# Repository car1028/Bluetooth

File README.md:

Bluetooth
=========

Bluetooth with AtMega

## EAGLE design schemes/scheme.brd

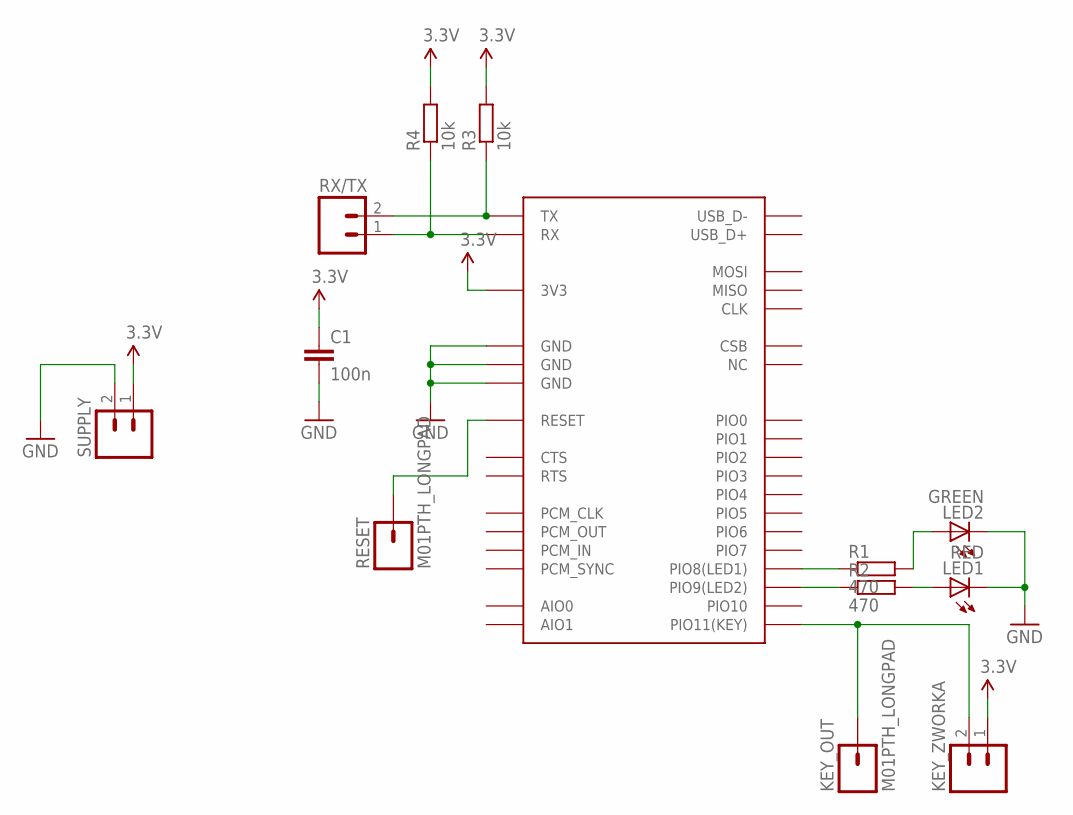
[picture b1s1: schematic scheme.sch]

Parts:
C1: 100n; C0805
IC1: HC-05
KEY_OUT: M01PTH_LONGPAD; 1X01_LONGPAD
KEY_ZWORKA: M02; 1X02_LONGPADS
LED1: RED; CHIPLED_0805
LED2: GREEN; CHIPLED_0805
R1, R2: 470; R0805
R3, R4: 10k; R0805
RESET: M01PTH_LONGPAD; 1X01_LONGPAD
RX/TX: M02; 1X02_LONGPADS
SUPPLY: M02; 1X02_LONGPADS

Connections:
3.3V: C1.1, IC1.3V3, KEY_ZWORKA.1, R3.2, R4.2, SUPPLY.1
GND: C1.2, IC1.GND@1 (GND), IC1.GND@2 (GND), IC1.GND@3 (GND), LED1.C, LED2.C, SUPPLY.2
unnamed: IC1.PIO11(KEY), KEY_OUT.1, KEY_ZWORKA.2
unnamed: IC1.PIO8(LED1), R1.1
unnamed: IC1.PIO9(LED2), R2.1
unnamed: LED2.A, R1.2
unnamed: LED1.A, R2.2
unnamed: IC1.RESET, RESET.1
unnamed: IC1.TX, R3.1, RX/TX.2
unnamed: IC1.RX, R4.1, RX/TX.1

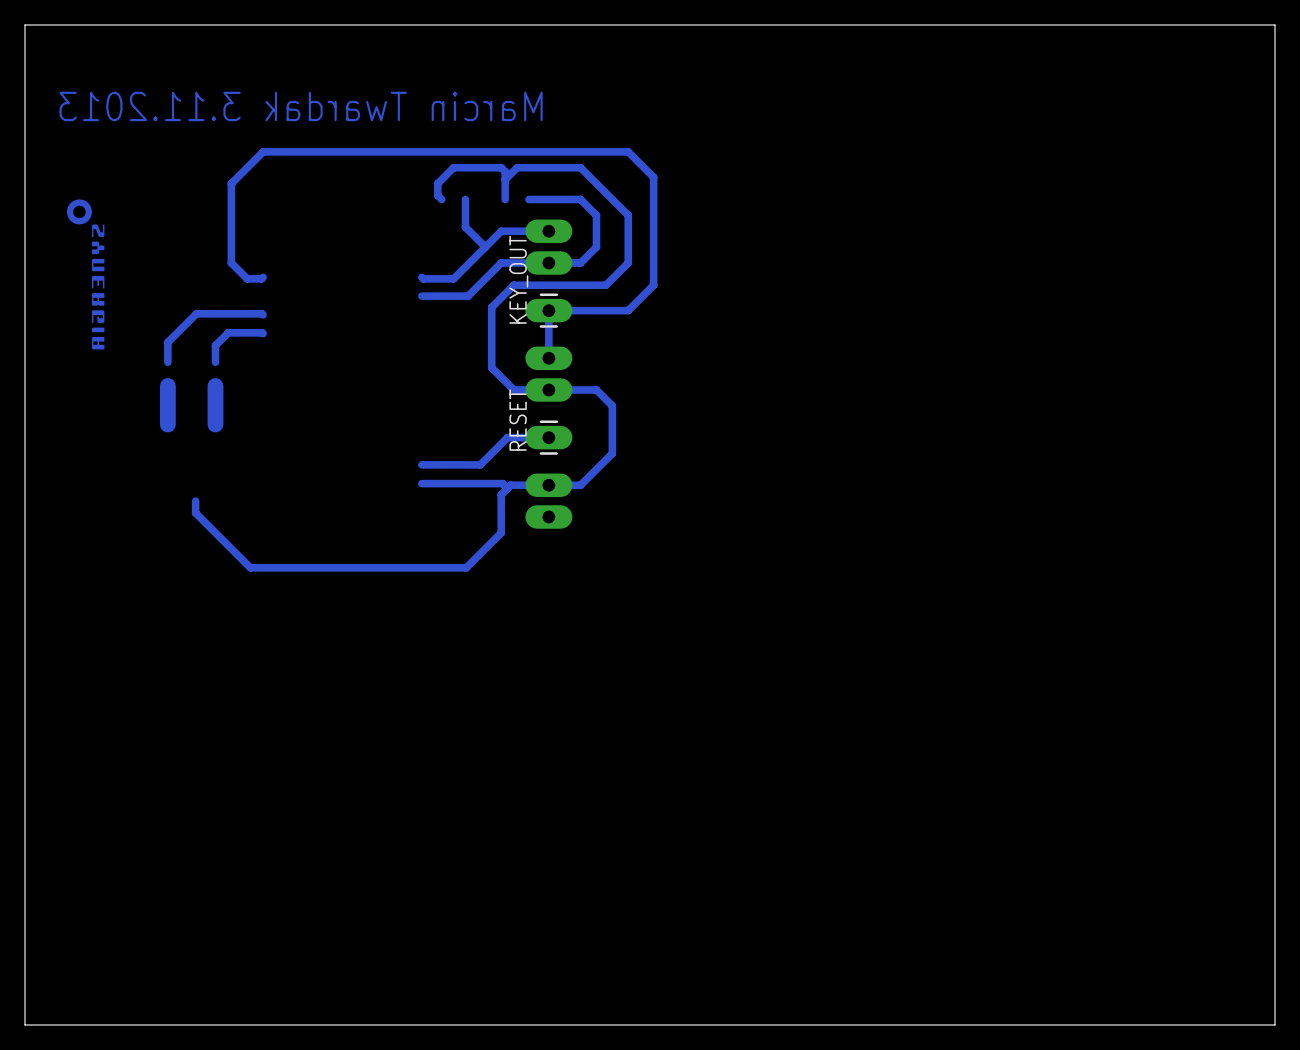
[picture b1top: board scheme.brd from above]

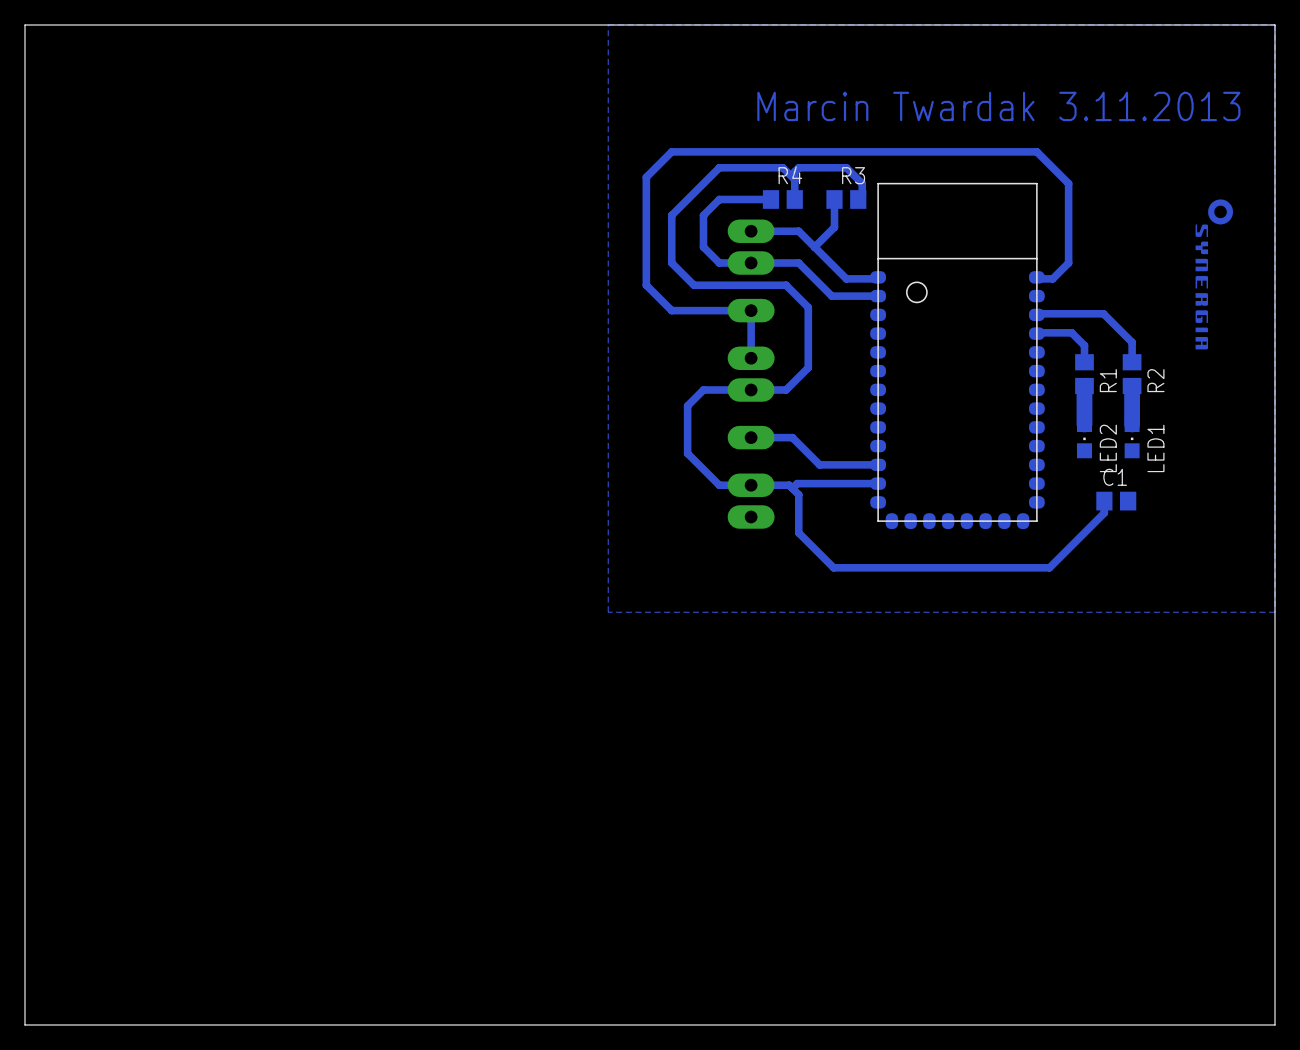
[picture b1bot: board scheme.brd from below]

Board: 2 copper layers, 100.0 x 80.0 mm, 14 parts (9 on the bottom side), 10 nets.

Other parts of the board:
U$1: SYNERGIA_12MM

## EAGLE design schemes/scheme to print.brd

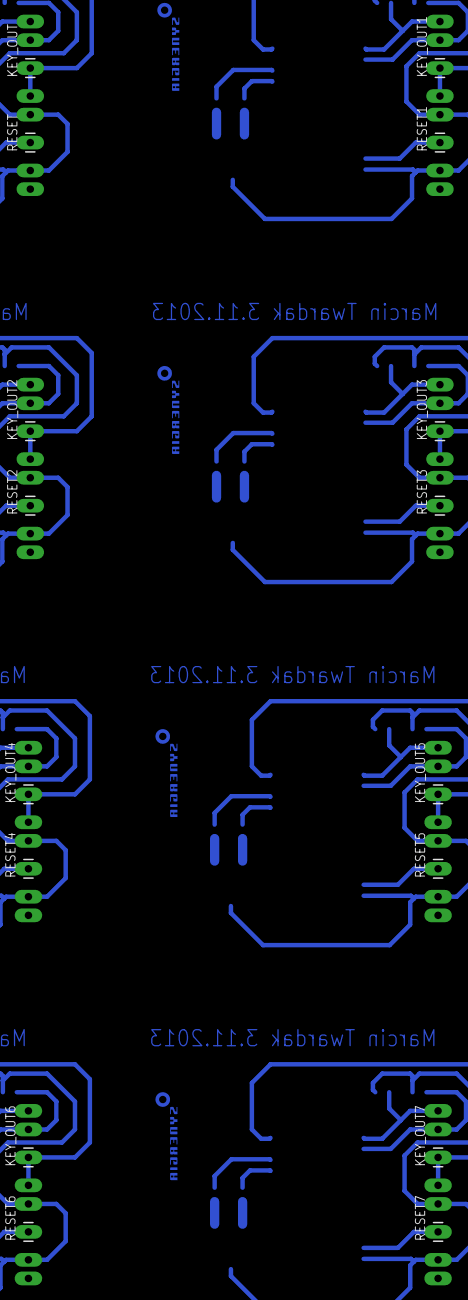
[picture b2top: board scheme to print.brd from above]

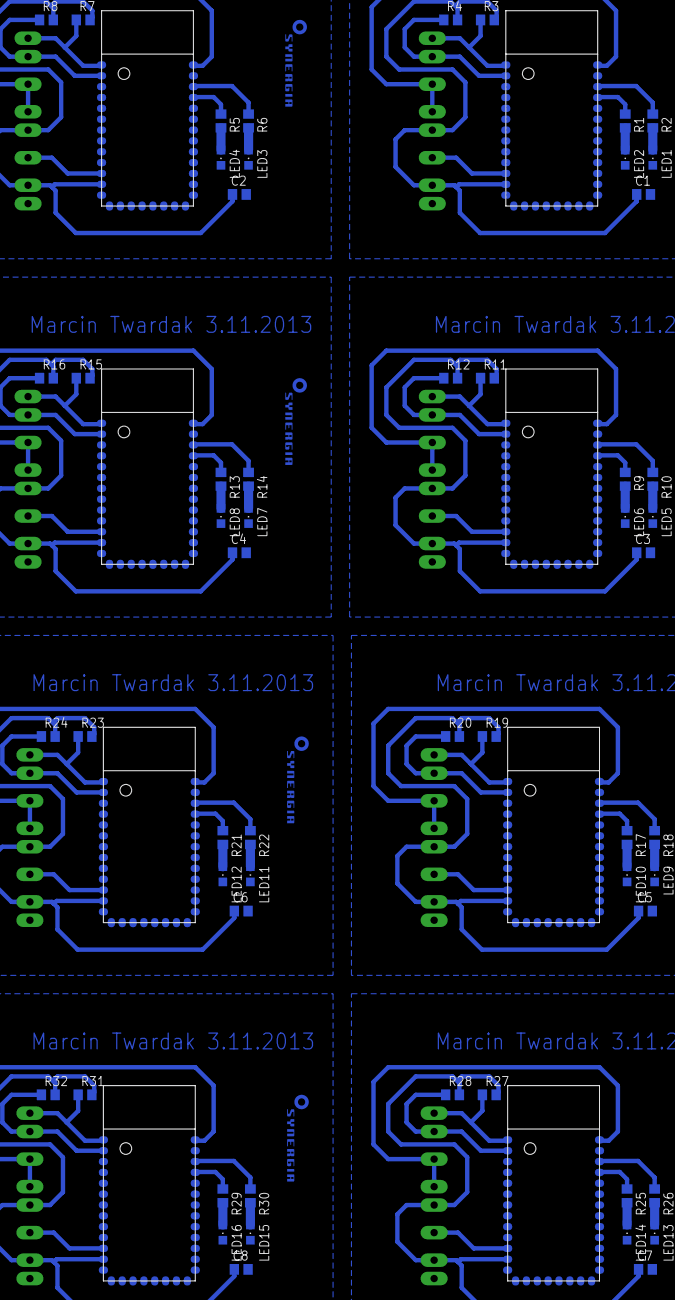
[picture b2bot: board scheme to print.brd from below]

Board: 2 copper layers, 112 parts (72 on the bottom side), 80 nets.

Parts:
C1, C2, C3, C4, C5, C6, C7, C8: 100n; C0805
IC1, IC2, IC3, IC4, IC5, IC6, IC7, IC8: HC-05
KEY_OUT, KEY_OUT1, KEY_OUT2, KEY_OUT3, KEY_OUT4, KEY_OUT5, KEY_OUT6, KEY_OUT7: M01PTH_LONGPAD; 1X01_LONGPAD
KEY_ZWORKA, KEY_ZWORKA1, KEY_ZWORKA2, KEY_ZWORKA3, KEY_ZWORKA4, KEY_ZWORKA5, KEY_ZWORKA6, KEY_ZWORKA7: 1X02_LONGPADS
LED1, LED3, LED5, LED7, LED9, LED11, LED13, LED15: RED; CHIPLED_0805
LED2, LED4, LED6, LED8, LED10, LED12, LED14, LED16: GREEN; CHIPLED_0805
R1, R2, R5, R6, R9, R10, R13, R14, R17, R18, R21, R22, R25, R26, R29, R30: 470; R0805
R3, R4, R7, R8, R11, R12, R15, R16, R19, R20, R23, R24, R27, R28, R31, R32: 10k; R0805
RESET, RESET1, RESET2, RESET3, RESET4, RESET5, RESET6, RESET7: M01PTH_LONGPAD; 1X01_LONGPAD
RX/TX, RX/TX1, RX/TX2, RX/TX3, RX/TX4, RX/TX5, RX/TX6, RX/TX7: 1X02_LONGPADS
SUPPLY, SUPPLY1, SUPPLY2, SUPPLY3, SUPPLY4, SUPPLY5, SUPPLY6, SUPPLY7: 1X02_LONGPADS
U$1, U$2, U$3, U$4, U$5, U$6, U$7, U$8: SYNERGIA_12MM

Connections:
3.3V: C1.1, IC1.3V3, KEY_ZWORKA.1, R3.2, R4.2, SUPPLY.1
3.3V1: C2.1, IC2.3V3, KEY_ZWORKA1.1, R7.2, R8.2, SUPPLY1.1
3.3V2: C3.1, IC3.3V3, KEY_ZWORKA2.1, R11.2, R12.2, SUPPLY2.1
3.3V3: C4.1, IC4.3V3, KEY_ZWORKA3.1, R15.2, R16.2, SUPPLY3.1
3.3V4: C5.1, IC5.3V3, KEY_ZWORKA4.1, R19.2, R20.2, SUPPLY4.1
3.3V5: C6.1, IC6.3V3, KEY_ZWORKA5.1, R23.2, R24.2, SUPPLY5.1
3.3V6: C7.1, IC7.3V3, KEY_ZWORKA6.1, R27.2, R28.2, SUPPLY6.1
3.3V7: C8.1, IC8.3V3, KEY_ZWORKA7.1, R31.2, R32.2, SUPPLY7.1
GND: C1.2, IC1.GND@1, IC1.GND@2, IC1.GND@3, LED1.C, LED2.C, SUPPLY.2
GND1: C2.2, IC2.GND@1, IC2.GND@2, IC2.GND@3, LED3.C, LED4.C, SUPPLY1.2
GND2: C3.2, IC3.GND@1, IC3.GND@2, IC3.GND@3, LED5.C, LED6.C, SUPPLY2.2
GND3: C4.2, IC4.GND@1, IC4.GND@2, IC4.GND@3, LED7.C, LED8.C, SUPPLY3.2
GND4: C5.2, IC5.GND@1, IC5.GND@2, IC5.GND@3, LED9.C, LED10.C, SUPPLY4.2
GND5: C6.2, IC6.GND@1, IC6.GND@2, IC6.GND@3, LED11.C, LED12.C, SUPPLY5.2
GND6: C7.2, IC7.GND@1, IC7.GND@2, IC7.GND@3, LED13.C, LED14.C, SUPPLY6.2
GND7: C8.2, IC8.GND@1, IC8.GND@2, IC8.GND@3, LED15.C, LED16.C, SUPPLY7.2
unnamed: IC1.PIO11(KEY), KEY_OUT.1, KEY_ZWORKA.2
unnamed: IC1.PIO8(LED1), R1.1
unnamed: IC1.PIO9(LED2), R2.1
unnamed: LED2.A, R1.2
unnamed: LED1.A, R2.2
unnamed: IC1.RESET, RESET.1
unnamed: IC1.TX, R3.1, RX/TX.2
unnamed: IC1.RX, R4.1, RX/TX.1
unnamed: IC2.PIO11(KEY), KEY_OUT1.1, KEY_ZWORKA1.2
unnamed: IC2.PIO8(LED1), R5.1
unnamed: IC2.PIO9(LED2), R6.1
unnamed: LED3.A, R6.2
unnamed: LED4.A, R5.2
unnamed: IC2.TX, R7.1, RX/TX1.2
unnamed: IC2.RX, R8.1, RX/TX1.1
unnamed: IC2.RESET, RESET1.1
unnamed: IC3.PIO11(KEY), KEY_OUT2.1, KEY_ZWORKA2.2
unnamed: IC3.PIO8(LED1), R9.1
unnamed: IC3.PIO9(LED2), R10.1
unnamed: LED5.A, R10.2
unnamed: LED6.A, R9.2
unnamed: IC3.TX, R11.1, RX/TX2.2
unnamed: IC3.RX, R12.1, RX/TX2.1
unnamed: IC3.RESET, RESET2.1
unnamed: IC4.PIO11(KEY), KEY_OUT3.1, KEY_ZWORKA3.2
unnamed: IC4.PIO8(LED1), R13.1
unnamed: IC4.PIO9(LED2), R14.1
unnamed: LED7.A, R14.2
unnamed: LED8.A, R13.2
unnamed: IC4.TX, R15.1, RX/TX3.2
unnamed: IC4.RX, R16.1, RX/TX3.1
unnamed: IC4.RESET, RESET3.1
unnamed: IC5.PIO11(KEY), KEY_OUT4.1, KEY_ZWORKA4.2
unnamed: IC5.PIO8(LED1), R17.1
unnamed: IC5.PIO9(LED2), R18.1
unnamed: LED9.A, R18.2
unnamed: LED10.A, R17.2
unnamed: IC5.TX, R19.1, RX/TX4.2
unnamed: IC5.RX, R20.1, RX/TX4.1
unnamed: IC5.RESET, RESET4.1
unnamed: IC6.PIO11(KEY), KEY_OUT5.1, KEY_ZWORKA5.2
unnamed: IC6.PIO8(LED1), R21.1
unnamed: IC6.PIO9(LED2), R22.1
unnamed: LED11.A, R22.2
unnamed: LED12.A, R21.2
unnamed: IC6.TX, R23.1, RX/TX5.2
unnamed: IC6.RX, R24.1, RX/TX5.1
unnamed: IC6.RESET, RESET5.1
unnamed: IC7.PIO11(KEY), KEY_OUT6.1, KEY_ZWORKA6.2
unnamed: IC7.PIO8(LED1), R25.1
unnamed: IC7.PIO9(LED2), R26.1
unnamed: LED13.A, R26.2
unnamed: LED14.A, R25.2
unnamed: IC7.TX, R27.1, RX/TX6.2
unnamed: IC7.RX, R28.1, RX/TX6.1
unnamed: IC7.RESET, RESET6.1
unnamed: IC8.PIO11(KEY), KEY_OUT7.1, KEY_ZWORKA7.2
unnamed: IC8.PIO8(LED1), R29.1
unnamed: IC8.PIO9(LED2), R30.1
unnamed: LED15.A, R30.2
unnamed: LED16.A, R29.2
unnamed: IC8.TX, R31.1, RX/TX7.2
unnamed: IC8.RX, R32.1, RX/TX7.1
unnamed: IC8.RESET, RESET7.1

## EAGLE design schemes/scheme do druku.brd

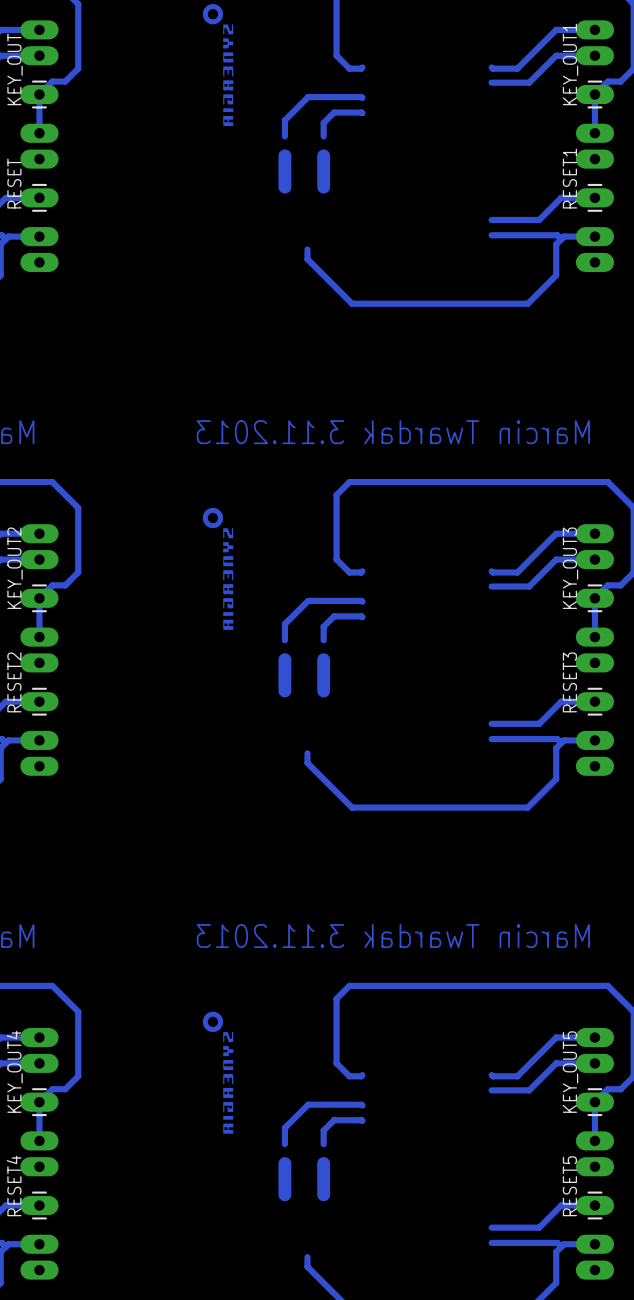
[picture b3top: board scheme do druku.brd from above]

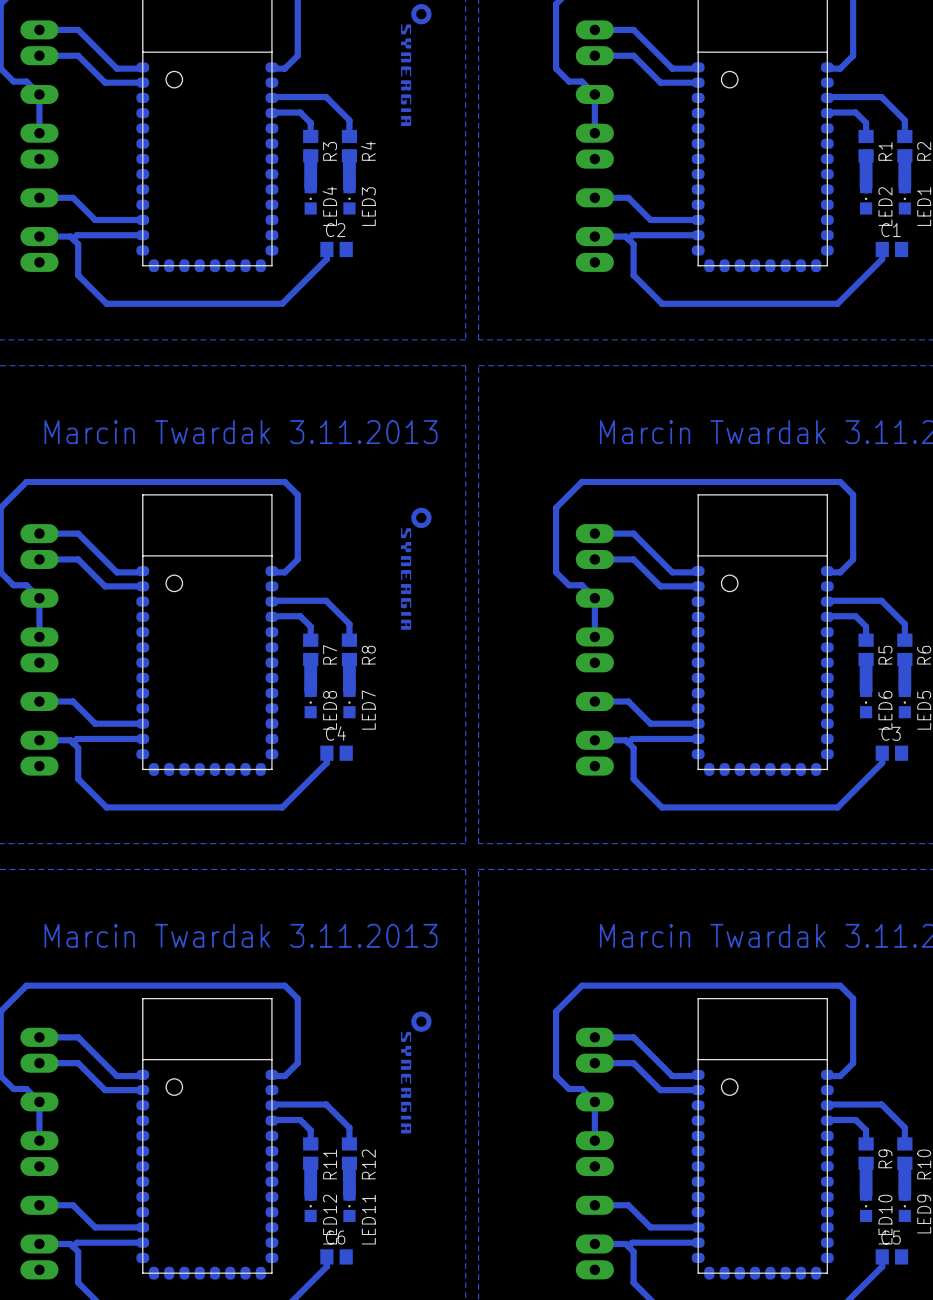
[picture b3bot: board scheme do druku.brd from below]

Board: 2 copper layers, 72 parts (42 on the bottom side), 60 nets.

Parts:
C1, C2, C3, C4, C5, C6: 100n; C0805
IC1, IC2, IC3, IC4, IC5, IC6: HC-05
KEY_OUT, KEY_OUT1, KEY_OUT2, KEY_OUT3, KEY_OUT4, KEY_OUT5: M01PTH_LONGPAD; 1X01_LONGPAD
KEY_ZWORKA, KEY_ZWORKA1, KEY_ZWORKA2, KEY_ZWORKA3, KEY_ZWORKA4, KEY_ZWORKA5: 1X02_LONGPADS
LED1, LED3, LED5, LED7, LED9, LED11: RED; CHIPLED_0805
LED2, LED4, LED6, LED8, LED10, LED12: GREEN; CHIPLED_0805
R1, R2, R3, R4, R5, R6, R7, R8, R9, R10, R11, R12: 470; R0805
RESET, RESET1, RESET2, RESET3, RESET4, RESET5: M01PTH_LONGPAD; 1X01_LONGPAD
RX/TX, RX/TX1, RX/TX2, RX/TX3, RX/TX4, RX/TX5: 1X02_LONGPADS
SUPPLY, SUPPLY1, SUPPLY2, SUPPLY3, SUPPLY4, SUPPLY5: 1X02_LONGPADS
U$1, U$2, U$3, U$4, U$5, U$6: SYNERGIA_12MM

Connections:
3.3V: C1.1, IC1.3V3, KEY_ZWORKA.1, SUPPLY.1
3.3V1: C2.1, IC2.3V3, KEY_ZWORKA1.1, SUPPLY1.1
3.3V2: C3.1, IC3.3V3, KEY_ZWORKA2.1, SUPPLY2.1
3.3V3: C4.1, IC4.3V3, KEY_ZWORKA3.1, SUPPLY3.1
3.3V4: C5.1, IC5.3V3, KEY_ZWORKA4.1, SUPPLY4.1
3.3V5: C6.1, IC6.3V3, KEY_ZWORKA5.1, SUPPLY5.1
GND: C1.2, IC1.GND@1, IC1.GND@2, IC1.GND@3, LED1.C, LED2.C, SUPPLY.2
GND1: C2.2, IC2.GND@1, IC2.GND@2, IC2.GND@3, LED3.C, LED4.C, SUPPLY1.2
GND2: C3.2, IC3.GND@1, IC3.GND@2, IC3.GND@3, LED5.C, LED6.C, SUPPLY2.2
GND3: C4.2, IC4.GND@1, IC4.GND@2, IC4.GND@3, LED7.C, LED8.C, SUPPLY3.2
GND4: C5.2, IC5.GND@1, IC5.GND@2, IC5.GND@3, LED9.C, LED10.C, SUPPLY4.2
GND5: C6.2, IC6.GND@1, IC6.GND@2, IC6.GND@3, LED11.C, LED12.C, SUPPLY5.2
unnamed: IC1.PIO11(KEY), KEY_OUT.1, KEY_ZWORKA.2
unnamed: IC1.PIO8(LED1), R1.1
unnamed: IC1.PIO9(LED2), R2.1
unnamed: LED2.A, R1.2
unnamed: LED1.A, R2.2
unnamed: IC1.RESET, RESET.1
unnamed: IC1.TX, RX/TX.2
unnamed: IC1.RX, RX/TX.1
unnamed: IC2.PIO11(KEY), KEY_OUT1.1, KEY_ZWORKA1.2
unnamed: IC2.PIO8(LED1), R3.1
unnamed: IC2.PIO9(LED2), R4.1
unnamed: LED3.A, R4.2
unnamed: LED4.A, R3.2
unnamed: IC2.TX, RX/TX1.2
unnamed: IC2.RX, RX/TX1.1
unnamed: IC2.RESET, RESET1.1
unnamed: IC3.PIO11(KEY), KEY_OUT2.1, KEY_ZWORKA2.2
unnamed: IC3.PIO8(LED1), R5.1
unnamed: IC3.PIO9(LED2), R6.1
unnamed: LED5.A, R6.2
unnamed: LED6.A, R5.2
unnamed: IC3.TX, RX/TX2.2
unnamed: IC3.RX, RX/TX2.1
unnamed: IC3.RESET, RESET2.1
unnamed: IC4.PIO11(KEY), KEY_OUT3.1, KEY_ZWORKA3.2
unnamed: IC4.PIO8(LED1), R7.1
unnamed: IC4.PIO9(LED2), R8.1
unnamed: LED7.A, R8.2
unnamed: LED8.A, R7.2
unnamed: IC4.TX, RX/TX3.2
unnamed: IC4.RX, RX/TX3.1
unnamed: IC4.RESET, RESET3.1
unnamed: IC5.PIO11(KEY), KEY_OUT4.1, KEY_ZWORKA4.2
unnamed: IC5.PIO8(LED1), R9.1
unnamed: IC5.PIO9(LED2), R10.1
unnamed: LED9.A, R10.2
unnamed: LED10.A, R9.2
unnamed: IC5.TX, RX/TX4.2
unnamed: IC5.RX, RX/TX4.1
unnamed: IC5.RESET, RESET4.1
unnamed: IC6.PIO11(KEY), KEY_OUT5.1, KEY_ZWORKA5.2
unnamed: IC6.PIO8(LED1), R11.1
unnamed: IC6.PIO9(LED2), R12.1
unnamed: LED11.A, R12.2
unnamed: LED12.A, R11.2
unnamed: IC6.TX, RX/TX5.2
unnamed: IC6.RX, RX/TX5.1
unnamed: IC6.RESET, RESET5.1

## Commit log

2013-10-25 empty scheme
2013-10-25 Created empty library
2013-10-28 Zakończony symbol
2013-10-28 HC-05 device done
2013-10-28 Names visibility improves
2013-11-03 Scheme done
2013-11-03 Board done
2013-11-03 ready to print
2013-11-03 pull-up resistors

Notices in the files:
parts and their libraries:
SparkFun: Licensing: CC v3.0 Share-Alike You are welcome to use this library for commercial purposes.
